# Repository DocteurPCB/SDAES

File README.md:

# SDAES — cartouche SD pour Neo Geo AES

Cartouche ouverte pour Neo Geo **AES** qui charge les jeux depuis une carte
microSD, dans l'esprit de la NeoSD : un menu s'affiche sur la console, on
choisit un fichier `.neo`, la cartouche le charge en mémoire et la console
redémarre dessus. **Tous les composants se soudent au fer** : aucun BGA ni
QFN.

> **État : conception + logiciel vérifiés en simulation, pas encore de
> prototype matériel.** Le code FPGA, le menu, le firmware et les outils sont
> écrits et testés automatiquement (voir plus bas) ; les circuits imprimés
> restent à dessiner. Le brochage AES est relevé sur le wiki neogeodev
> (`hardware/aes_connector.csv`) ; son orientation reste à confirmer sur une
> vraie cartouche (`docs/07-validation-et-feuille-de-route.md`).

## Principe

* **4 FPGA Lattice iCE40 en TQFP-144** (un par bus de la console : programme
  68000, son ADPCM, sprites, couche fixe + Z80) répondent en temps réel et
  remplacent les ROM et les puces de cartouche (NEO-273, NEO-ZMC2,
  NEO-PCM2, banques P et Z80). Chaîne de développement libre (Yosys,
  nextpnr).
* **3 SDRAM + 1 SRAM en TSOP** contiennent le jeu (jusqu'à 24 Mo de P,
  32 Mo de V, 64 Mo de C : tous les jeux commerciaux standards).
* Un **Raspberry Pi Pico 2 (RP2350, ~5 €)** lit la carte SD et charge les
  jeux (~9 Mo/s). Un Raspberry Pi « Linux » ne convient pas pour le bus
  lui-même (trop peu de GPIO, latence) : voir `docs/01-architecture.md`.
* Coût matière estimé : **≈ 70-95 € par cartouche** en petite série,
  montage à la main.

## Organisation du dépôt

| Dossier | Contenu |
|---|---|
| `docs/` | architecture, signaux, timings, liaison, menu/firmware, nomenclature, validation |
| `hdl/` | Verilog des 4 FPGA (`prog/` : P et V, `cha/` : C et SM, `common/`) + bancs de test (`sim/`) |
| `menu/` | menu Neo Geo : programme 68000 (`68k/`) et pilote Z80 (`z80/`) |
| `firmware/rp2350/` | firmware du Pico 2 (SDK Pico + FatFs SDIO) et test sur PC |
| `protocol/` | protocole menu ↔ RP2350, partagé |
| `tools/` | `neotool.py` (.neo, police, BRAM, code de sécurité, bootlegs avec `mame_sets.py`), tests |
| `hardware/` | brochage du connecteur AES (`aes_connector.csv`), gabarits de contraintes FPGA (`.pcf`), futurs projets KiCad |

## Construire et tester

Dépendances (Ubuntu/Debian) : `iverilog`, `gcc-m68k-linux-gnu`, `z80asm`,
`console-setup-linux` (police), Python 3 ; facultatif : `yosys` +
`nextpnr-ice40` (ou `pip install yowasp-yosys yowasp-nextpnr-ice40`),
`pip install machine68k` (émulation du menu).

```
make                               # menu + fichiers d'init BRAM (hdl/build/*.hex)
make SECURITY_FROM=un_jeu.neo      # idem, avec le code de sécurité requis par le BIOS
make test                          # tous les tests (Python + simulations HDL)
make sdaes_test.neo                # ROM de test à copier sur la carte SD
make -C hdl lint pnr YOSYS=yowasp-yosys NEXTPNR=yowasp-nextpnr-ice40   # synthèse + placement-routage des 4 FPGA
python3 tools/neotool.py info jeu.neo
```

Résultats actuels de `make test` :

* 18 tests Python : outils (dont descriptions de protections), firmware sur PC (chargement complet d'un `.neo`
  et comparaison des images mémoire), menu 68000 exécuté dans un émulateur ;
* simulations HDL au niveau carte : `tb_prog` (FPGA P + V) et `tb_cha`
  (FPGA C + SM) en SUCCÈS ; lecture du programme 68000 en 79 ns (126 ns au
  pire cas) pour une limite estimée à ~125-150 ns ;
* placement-routage des 4 FPGA à 101-114 MHz pour 100 MHz visés.

## Documentation

1. [Architecture](docs/01-architecture.md)
2. [Signaux et niveaux 5 V](docs/02-signaux-connecteurs.md)
3. [Mémoires et timings](docs/03-memoire-et-timings.md)
4. [Liaison RP2350 ↔ FPGA](docs/04-liaison-rp2350.md)
5. [Menu et firmware](docs/05-menu-et-firmware.md)
6. [Matériel et nomenclature](docs/06-materiel-nomenclature.md)
7. [Validation et feuille de route](docs/07-validation-et-feuille-de-route.md)
8. [Cartouches protégées](docs/08-cartouches-protegees.md)

## Avertissements

* Aucun BIOS, ROM ou code SNK n'est inclus. Le code de sécurité exigé par le
  BIOS est recopié, à la construction, depuis un jeu que vous possédez.
* Protections : SMA (KOF 99, Garou, Metal Slug 3, KOF 2000), PVC (Metal
  Slug 5, SVC Chaos, KOF 2003), KOF 98, PRO-CT0 (Fatal Fury 2, Super
  Sidekicks), Metal Slug X (P1 corrigée au chargement), Metal Slug 5 Plus
  et les bootlegs de Metal Slug 5, SVC Chaos et KOF 2003 sont pris en
  charge (`neotool mame` fabrique leurs `.neo`)
  ([détails](docs/08-cartouches-protegees.md)) ; les tables SMA s'extraient
  du source de MAME avec `neotool.py sma-from-mame`. Banques de couche fixe
  NEO-CMC : KOF 2000, SVC, KOF 2003, Metal Slug 3/4 ; approchées pour Garou.

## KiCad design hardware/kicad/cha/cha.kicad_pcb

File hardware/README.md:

# Matériel

Contraintes des 4 FPGA iCE40HX4K-TQ144 avec les **vrais numéros de
broches**, produites par `hardware/gen/fpga_pins.py` (ne pas modifier les
`.pcf` à la main) :

```
python3 hardware/gen/fpga_pins.py
make -C hdl pnr YOSYS=yowasp-yosys NEXTPNR=yowasp-nextpnr-ice40
```

| FPGA | Carte | E/S utilisées | Fréquence max (broches réelles) |
|---|---|---|---|
| P | PROG | 94 / 107 | 103,3 MHz |
| V | PROG | 80 / 107 | 102,2 MHz |
| C | CHA | 89 / 107 | 107,6 MHz |
| SM | CHA | 92 / 107 | 108,8 MHz |

## Règles de placement des broches

* Signaux du connecteur (via les tampons de niveaux) sur les bancs 3 et 2
  (côtés gauche et bas du boîtier) ; mémoire, liaison RP2350, MODE et LED
  sur les bancs 0 et 1.
* `CLK25` sur l'entrée globale GBIN3 (broche 93).
* Broche 129 réservée à une sortie : la PLL du haut, utilisée par le
  design, réquisitionne son chemin d'entrée (de même la broche 49 pour la
  PLL du bas).
* Pas de flash : le RP2350 configure les FPGA en SPI esclave par le bus
  de liaison. `LK_SCK` sur la broche 70 (SCK), `LK_IO[0]` sur 68 (SDI),
  `LK_CS_N` sur 71 (SS) ; elles redeviennent ces entrées après la
  configuration. 67 (SDO) ne sert qu'au connecteur de secours.
* Signaux utilisés **comme horloges** dans le HDL — à placer sur des
  entrées globales (GBIN) : `CLK_12M`, `PCK1B` (FPGA C) ; `PCK2B` (SM) ;
  `SDRMPX`, `SDPMPX` (V).
* SDRAM regroupée sur un même côté du boîtier, `SD_CLK` en sortie DDR
  (SB_IO) avec résistance série.
* Bancs d'E/S en 3,3 V ; VPP de l'iCE40 relié au 3,3 V.

## Schémas KiCad (cartes PROG et CHA)

Les schémas sont **générés** à partir d'une description Python des deux
cartes (`hardware/gen/boards.py`), puis vérifiés par KiCad :

```
sudo apt-get install kicad kicad-symbols kicad-footprints     # KiCad 7
python3 hardware/gen/boards.py --check --pdf
```

* `hardware/kicad/prog/`, `hardware/kicad/cha/` : projets KiCad (une
  feuille par bloc : connecteur et alimentations, tampons de niveaux,
  FPGA, mémoires, RP2350 et carte SD).
* `hardware/kicad/sdaes_prog.pdf`, `sdaes_cha.pdf` : schémas en PDF.
* `hardware/kicad/sdaes.kicad_sym`, `sdaes.pretty` : symboles et empreintes
  propres au projet (connecteur de bord AES, Pico 2, 16244, SRAM).
* `--check` réexporte la netlist avec `kicad-cli` et la compare à la
  description : elle doit être **identique** (aucun réseau oublié ni
  ajouté). Aucun réseau ne doit toucher une seule broche.

Chaque broche porte une étiquette globale au nom de son signal (pas de
fils) : `AES_xxx` côté console (5 V), `xxx` côté FPGA, `P_`, `V_`, `C_`,
`SM_` pour les signaux locaux d'un FPGA. Les broches des FPGA viennent des
`.pcf` ci-dessus. Brochages hors bibliothèque KiCad relevés dans les fiches
TI (SN74LVC16244A, SN74AHCT16244 : identiques), ISSI (IS61WV10248EDBLL) et
Raspberry Pi (Pico 2).

| Carte | Composants | Réseaux |
|---|---|---|
| PROG | 124 | 274 |
| CHA | 138 | 293 |

Par FPGA : connecteur de secours 2 x 3 (configuration directe par
`iceprog -S`, RP2350 au repos), oscillateur 25 MHz, filtre RC des deux PLL
(100 Ω, 10 µF, 100 nF), découplage 100 nF par broche d'alimentation, LED.
Alimentations par carte : AMS1117-3.3 (5 V → 3,3 V) et AP2112K-1.2
(3,3 V → 1,2 V).

### Contours et connecteur de bord

`python3 hardware/gen/outline.py` (module Python de KiCad) écrit
`hardware/kicad/{prog,cha}/{prog,cha}.kicad_pcb` : contour, deux trous de
10 mm pour les plots de la coque et connecteur J1 placé. Cotes reprises des
cartes AES de jwestfall69 (`neogeo-diag-aes-prog`, `neogeo-diag-aes-cha`,
fabriquées et testées, domaine public ; ce sont des cartes de test du Z80,
reprises pour leur mécanique seulement), identiques à 0,01 mm près, et
recoupées sur la photo de la carte SNK NEO-AEG PROG-EP du wiki :

| | PROG | CHA |
|---|---|---|
| Corps | 174,0 x 115 mm | 173,0 x 115 mm |
| Languette (centrée) | 129,2 x 19 mm | 129,2 x 19 mm |
| Encoches 12 x 2,5 mm (bord supérieur) | à 36 mm de chaque bord | à 5,45 mm de chaque bord |
| Trous Ø 10 mm | ±45 mm de l'axe, 11,75 mm au-dessus de l'épaulement | idem |

Contacts : 1,5 x 10 mm au pas de 2,54 mm, centre à 7,1 mm du bord ; A1..A50
(repères T) sur la face composants, B1..B50 sur l'autre ; vu côté
composants, languette en bas, A1 et B1 à droite. Fabrication : 1,6 mm,
finition ENIG, contacts dorés chanfreinés à 45° : déclaré dans l'empilement
de la carte (connecteur de bord biseauté, repris dans le fichier `.gbrjob`)
et rappelé par une note sur la couche Cmts.User ; option « Gold fingers » +
« Beveled » à cocher à la commande. La carte CHA se loge
derrière la carte PROG : hauteur des composants limitée (jwestfall69 :
un support DIP ordinaire + EPROM est trop haut, un support bas passe).

### Circuits imprimés (4 couches)

```
python3 hardware/gen/pcb.py --pins     # placement + affectation des broches FPGA
python3 hardware/gen/fpga_pins.py      # .pcf (pins_opt.json prioritaire)
python3 hardware/gen/boards.py --check # schémas à jour
python3 hardware/gen/pcb.py            # placement final (répéter jusqu'à stabilité)
python3 hardware/gen/route.py prog     # Freerouting puis DRC (idem cha)
```

* `pcb.py` : empreintes et réseaux depuis `boards.py`, contour depuis
  `outline.py`. Ancres (circuits intégrés, connecteurs) à des positions
  fixées : contacts en bas, tampons de niveaux en rangée au-dessus (canaux
  dans l'ordre des contacts), FPGA au milieu, mémoires en haut ; carte PROG
  (côté avant de la cartouche) : Pico 2 au milieu, microSD et bouton sur le
  bord supérieur ; sous le Pico, ni piste ni via sur la face composants.
  Câble PROG-CHA au même endroit sur les deux cartes (x = 172 mm). Passifs placés au plus près de la broche de
  leur circuit. Empilement : F.Cu signaux, In1 plan de masse continu,
  In2 plan +3V3, B.Cu signaux ; +5V et +1V2 en pistes larges. Le 4
  couches est retenu pour la SDRAM à 100 MHz (fronts ~1 ns : chemin de
  retour sous chaque piste) et le découplage des FPGA ; surcoût de quelques
  euros par cartouche.
* `--pins` : chaque signal d'un FPGA est affecté à la broche tournée vers
  sa cible, en conservant l'ordre circulaire (pas de croisement à la
  sortie du boîtier) ; horloges sur leurs entrées GBIN, broche 129 en
  sortie seulement. Résultat dans `hardware/gen/pins_opt.json`, repris par
  `fpga_pins.py` ; le placement-routage FPGA (`make -C hdl pnr`) doit être
  relancé ensuite.
* `route.py` : export Specctra (couches internes déclarées « power »),
  Freerouting (2.4.1, Java 25), relecture de la session, remplissage des
  zones, DRC `kicad-cli`.

**À vérifier avant le routage** : boucles audio L/R reliées par
des résistances de 0 Ω (révision NEO-AES de la console), valeurs du filtre
PLL (note Lattice sur l'iCE40), courant réel des régulateurs.

## À faire

1. ~~Brochage et cotes des cartes AES PROG/CHA~~ (fait, voir plus haut).
2. ~~Schémas~~, ~~contours~~ (faits).
3. Routage 4 couches (en cours, `route.py`), contacts dorés chanfreinés.
4. Après un premier routage : remplacer la nappe PROG-CHA (J2 / J5, 2 x 7)
   par un connecteur carte à carte aligné sur les deux cartes, hauteur
   adaptée aux entretoises.
5. `make -C hdl bits` (bitstreams avec les broches réelles).

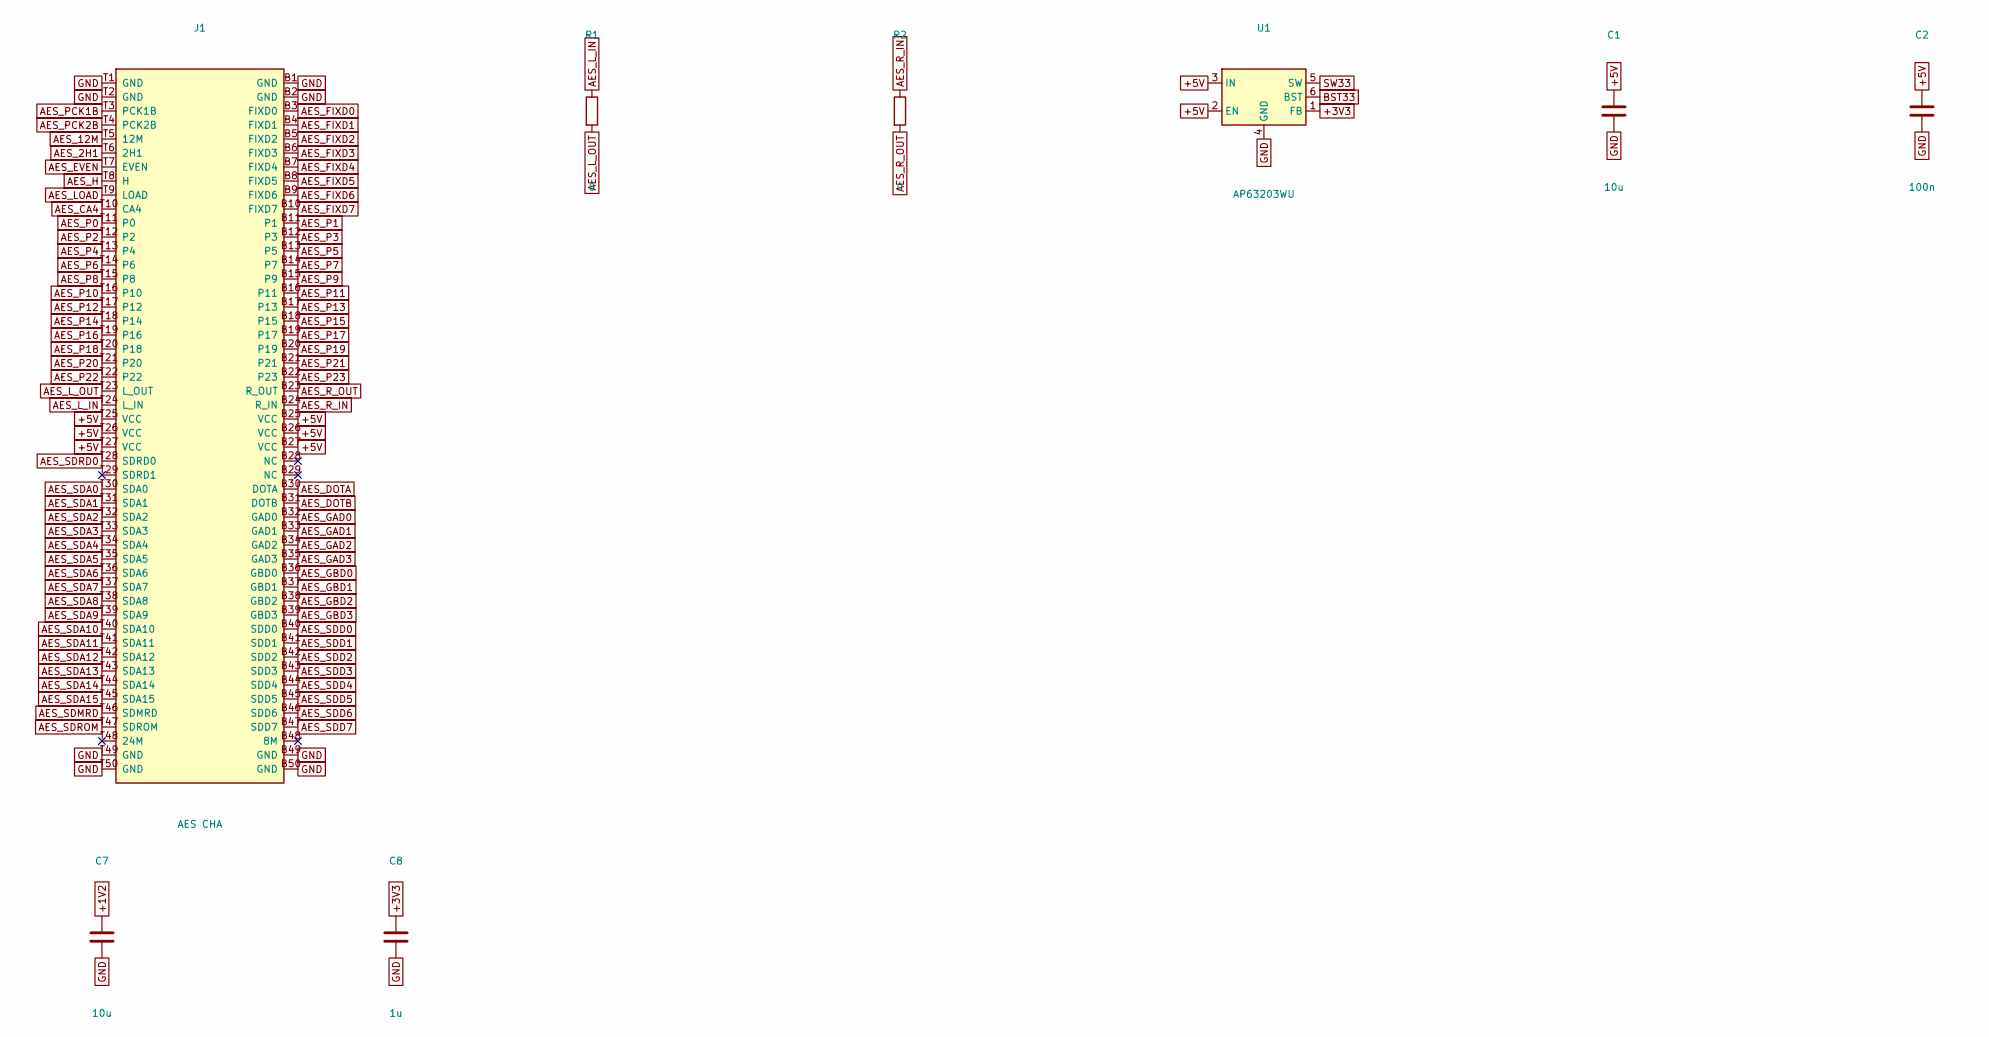
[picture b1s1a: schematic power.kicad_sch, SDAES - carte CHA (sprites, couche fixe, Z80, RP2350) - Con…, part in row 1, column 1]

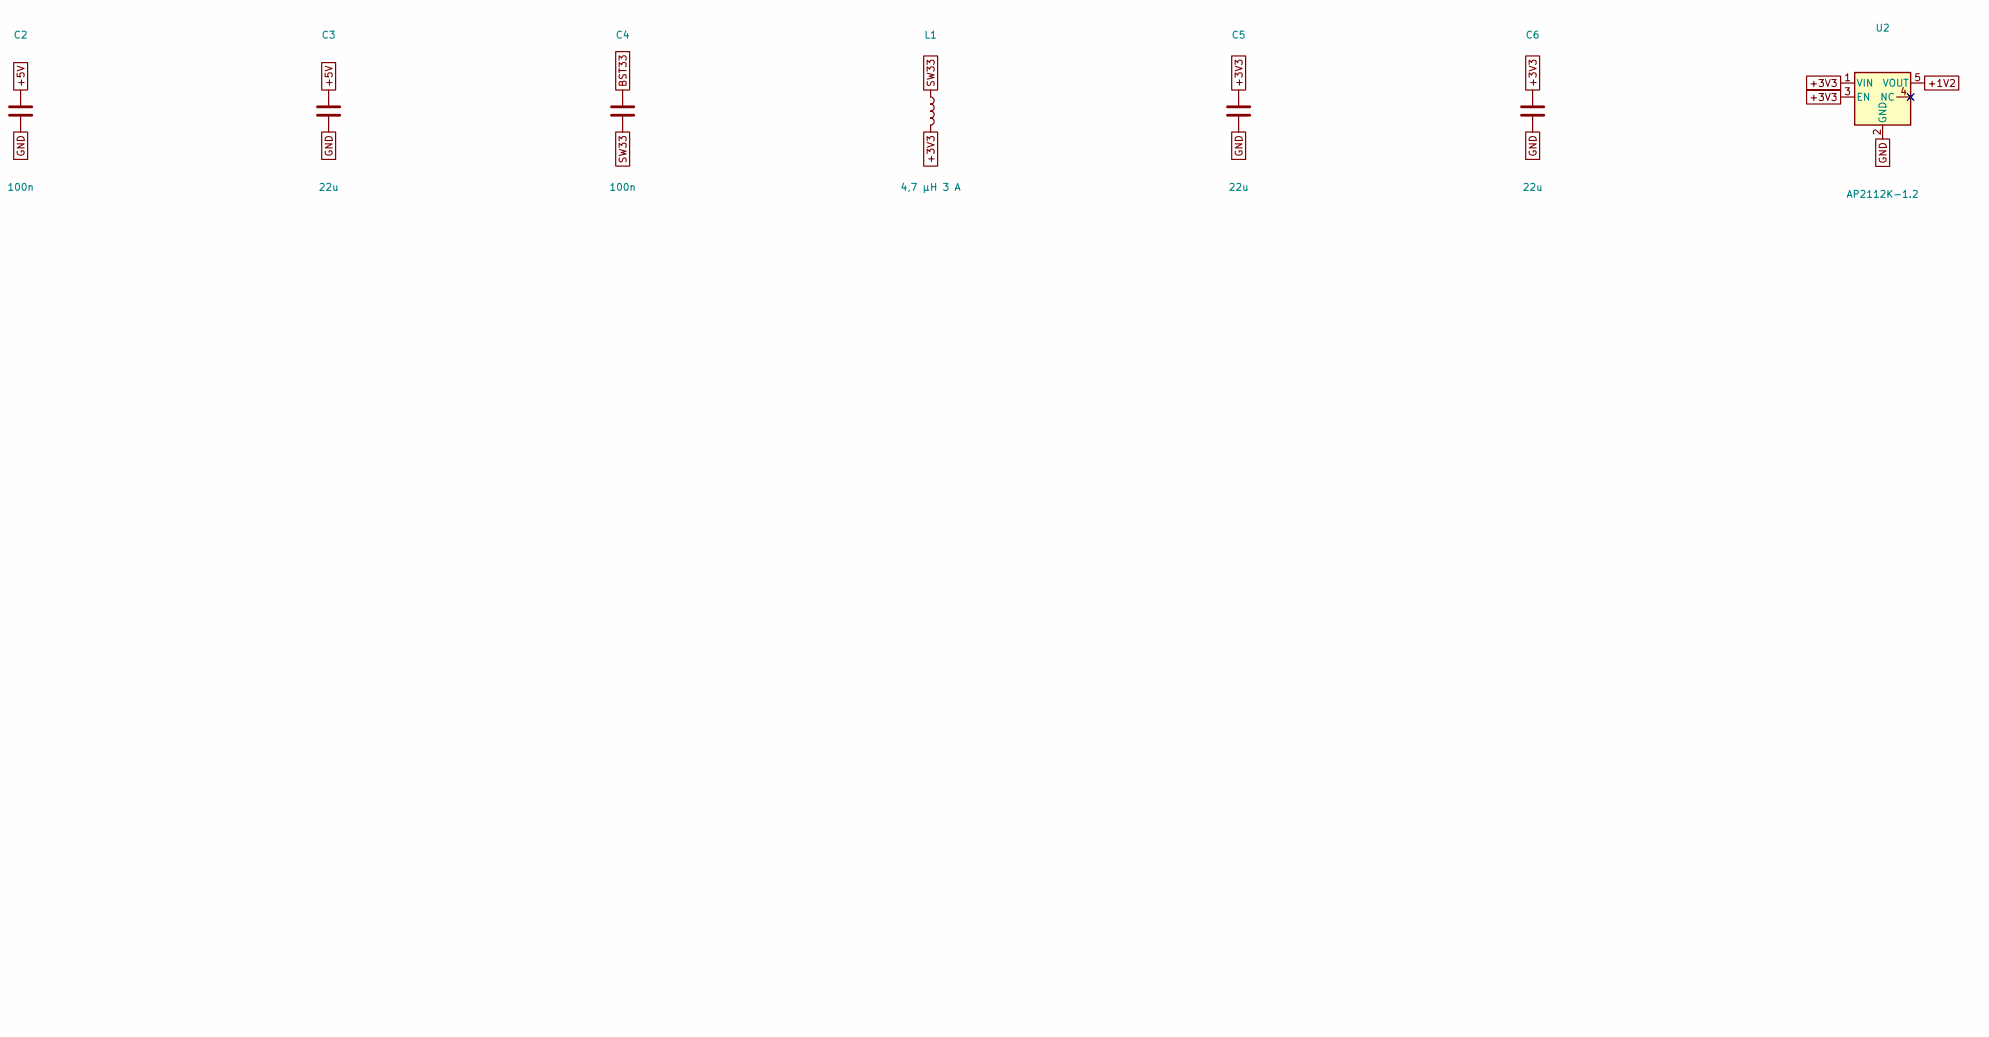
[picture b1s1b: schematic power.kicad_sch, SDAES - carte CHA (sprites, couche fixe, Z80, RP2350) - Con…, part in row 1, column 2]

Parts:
C1, C7: 10u; C_0805_2012Metric
C2, C4: 100n; C_0603_1608Metric
C3, C5, C6: 22u; C_1206_3216Metric
C8: 1u; C_0603_1608Metric
J1: AES CHA; AES_Edge_2x50_P2.54mm
L1: 4,7 µH 3 A; L_Bourns_SRP5030T
R1, R2: 0; R_0603_1608Metric
U1: AP63203WU; TSOT-23-6
U2: AP2112K-1.2; SOT-23-5

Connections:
+1V2: C7.1, U2.5 (VOUT); also elsewhere on the board
+3V3: C5.1, C6.1, C8.1, L1.2, U1.1 (FB), U2.1 (VIN), U2.3 (EN); also elsewhere on the board
+5V: C1.1, C2.1, C3.1, J1.B25 (VCC), J1.B26 (VCC), J1.B27 (VCC), J1.T25 (VCC), J1.T26 (VCC), J1.T27 (VCC), U1.2 (EN), U1.3 (IN); also elsewhere on the board
AES_2H1: J1.T6 (2H1); also elsewhere on the board
AES_12M: J1.T5 (12M); also elsewhere on the board
AES_CA4: J1.T10 (CA4); also elsewhere on the board
AES_DOTA: J1.B30 (DOTA); also elsewhere on the board
AES_DOTB: J1.B31 (DOTB); also elsewhere on the board
AES_EVEN: J1.T7 (EVEN); also elsewhere on the board
AES_FIXD0: J1.B3 (FIXD0); also elsewhere on the board
AES_FIXD1: J1.B4 (FIXD1); also elsewhere on the board
AES_FIXD2: J1.B5 (FIXD2); also elsewhere on the board
AES_FIXD3: J1.B6 (FIXD3); also elsewhere on the board
AES_FIXD4: J1.B7 (FIXD4); also elsewhere on the board
AES_FIXD5: J1.B8 (FIXD5); also elsewhere on the board
AES_FIXD6: J1.B9 (FIXD6); also elsewhere on the board
AES_FIXD7: J1.B10 (FIXD7); also elsewhere on the board
AES_GAD0: J1.B32 (GAD0); also elsewhere on the board
AES_GAD1: J1.B33 (GAD1); also elsewhere on the board
AES_GAD2: J1.B34 (GAD2); also elsewhere on the board
AES_GAD3: J1.B35 (GAD3); also elsewhere on the board
AES_GBD0: J1.B36 (GBD0); also elsewhere on the board
AES_GBD1: J1.B37 (GBD1); also elsewhere on the board
AES_GBD2: J1.B38 (GBD2); also elsewhere on the board
AES_GBD3: J1.B39 (GBD3); also elsewhere on the board
AES_H: J1.T8 (H); also elsewhere on the board
AES_LOAD: J1.T9 (LOAD); also elsewhere on the board
AES_L_IN: J1.T24 (L_IN), R1.1
AES_L_OUT: J1.T23 (L_OUT), R1.2
AES_P0: J1.T11 (P0); also elsewhere on the board
AES_P1: J1.B11 (P1); also elsewhere on the board
AES_P2: J1.T12 (P2); also elsewhere on the board
AES_P3: J1.B12 (P3); also elsewhere on the board
AES_P4: J1.T13 (P4); also elsewhere on the board
AES_P5: J1.B13 (P5); also elsewhere on the board
AES_P6: J1.T14 (P6); also elsewhere on the board
AES_P7: J1.B14 (P7); also elsewhere on the board
AES_P8: J1.T15 (P8); also elsewhere on the board
AES_P9: J1.B15 (P9); also elsewhere on the board
AES_P10: J1.T16 (P10); also elsewhere on the board
AES_P11: J1.B16 (P11); also elsewhere on the board
AES_P12: J1.T17 (P12); also elsewhere on the board
AES_P13: J1.B17 (P13); also elsewhere on the board
AES_P14: J1.T18 (P14); also elsewhere on the board
AES_P15: J1.B18 (P15); also elsewhere on the board
AES_P16: J1.T19 (P16); also elsewhere on the board
AES_P17: J1.B19 (P17); also elsewhere on the board
AES_P18: J1.T20 (P18); also elsewhere on the board
AES_P19: J1.B20 (P19); also elsewhere on the board
AES_P20: J1.T21 (P20); also elsewhere on the board
AES_P21: J1.B21 (P21); also elsewhere on the board
AES_P22: J1.T22 (P22); also elsewhere on the board
AES_P23: J1.B22 (P23); also elsewhere on the board
AES_PCK1B: J1.T3 (PCK1B); also elsewhere on the board
AES_PCK2B: J1.T4 (PCK2B); also elsewhere on the board
AES_R_IN: J1.B24 (R_IN), R2.1
AES_R_OUT: J1.B23 (R_OUT), R2.2
AES_SDA0: J1.T30 (SDA0); also elsewhere on the board
AES_SDA1: J1.T31 (SDA1); also elsewhere on the board
AES_SDA2: J1.T32 (SDA2); also elsewhere on the board
AES_SDA3: J1.T33 (SDA3); also elsewhere on the board
AES_SDA4: J1.T34 (SDA4); also elsewhere on the board
AES_SDA5: J1.T35 (SDA5); also elsewhere on the board
AES_SDA6: J1.T36 (SDA6); also elsewhere on the board
AES_SDA7: J1.T37 (SDA7); also elsewhere on the board
AES_SDA8: J1.T38 (SDA8); also elsewhere on the board
AES_SDA9: J1.T39 (SDA9); also elsewhere on the board
AES_SDA10: J1.T40 (SDA10); also elsewhere on the board
AES_SDA11: J1.T41 (SDA11); also elsewhere on the board
AES_SDA12: J1.T42 (SDA12); also elsewhere on the board
AES_SDA13: J1.T43 (SDA13); also elsewhere on the board
AES_SDA14: J1.T44 (SDA14); also elsewhere on the board
AES_SDA15: J1.T45 (SDA15); also elsewhere on the board
AES_SDD0: J1.B40 (SDD0); also elsewhere on the board
AES_SDD1: J1.B41 (SDD1); also elsewhere on the board
AES_SDD2: J1.B42 (SDD2); also elsewhere on the board
AES_SDD3: J1.B43 (SDD3); also elsewhere on the board
AES_SDD4: J1.B44 (SDD4); also elsewhere on the board
AES_SDD5: J1.B45 (SDD5); also elsewhere on the board
AES_SDD6: J1.B46 (SDD6); also elsewhere on the board
AES_SDD7: J1.B47 (SDD7); also elsewhere on the board
AES_SDMRD: J1.T46 (SDMRD); also elsewhere on the board
AES_SDRD0: J1.T28 (SDRD0); also elsewhere on the board
AES_SDROM: J1.T47 (SDROM); also elsewhere on the board
BST33: C4.1, U1.6 (BST)
GND: C1.2, C2.2, C3.2, C5.2, C6.2, C7.2, C8.2, J1.B1 (GND), J1.B2 (GND), J1.B49 (GND), J1.B50 (GND), J1.T1 (GND), J1.T2 (GND), J1.T49 (GND), J1.T50 (GND), U1.4 (GND), U2.2 (GND); also elsewhere on the board
SW33: C4.2, L1.1, U1.5 (SW)

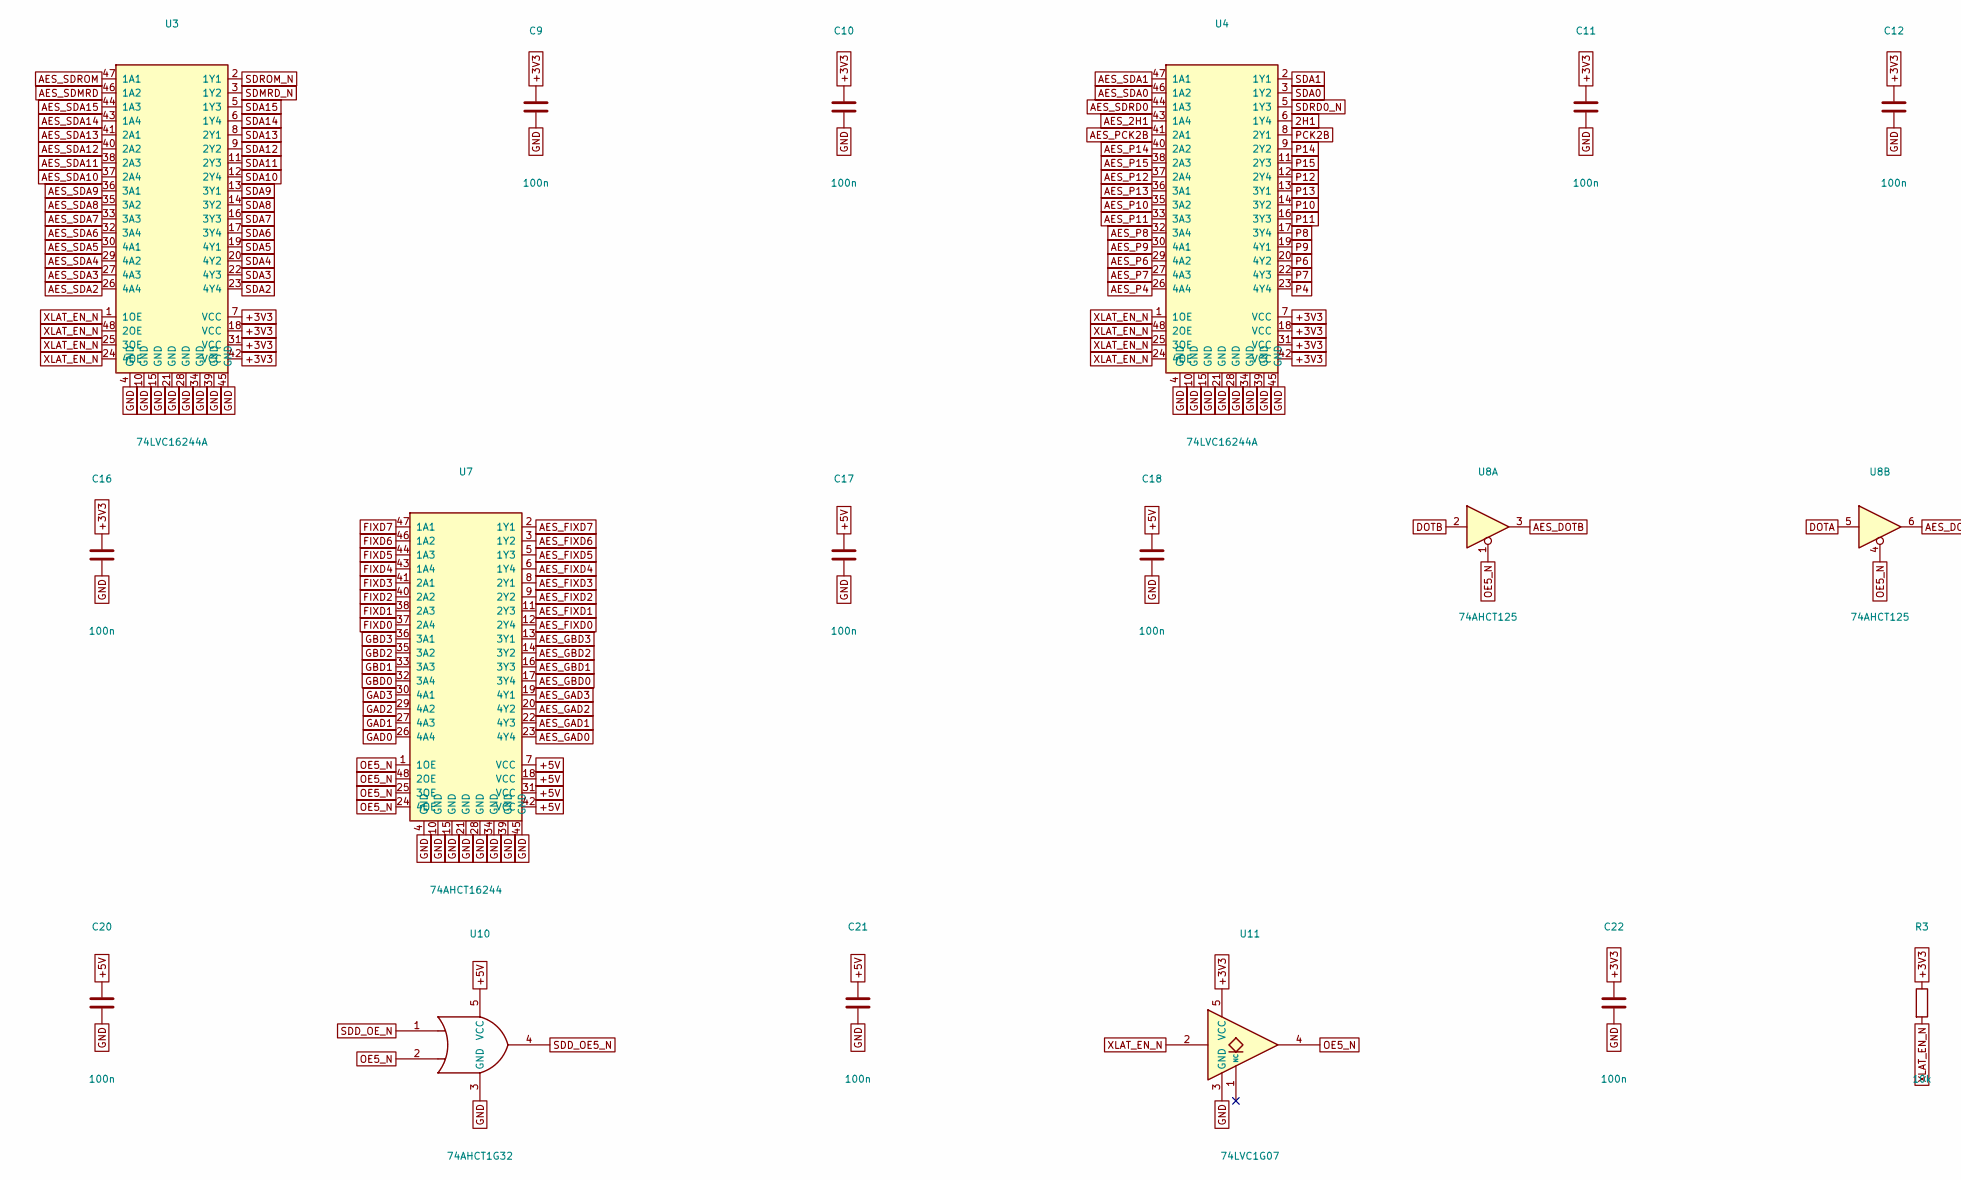
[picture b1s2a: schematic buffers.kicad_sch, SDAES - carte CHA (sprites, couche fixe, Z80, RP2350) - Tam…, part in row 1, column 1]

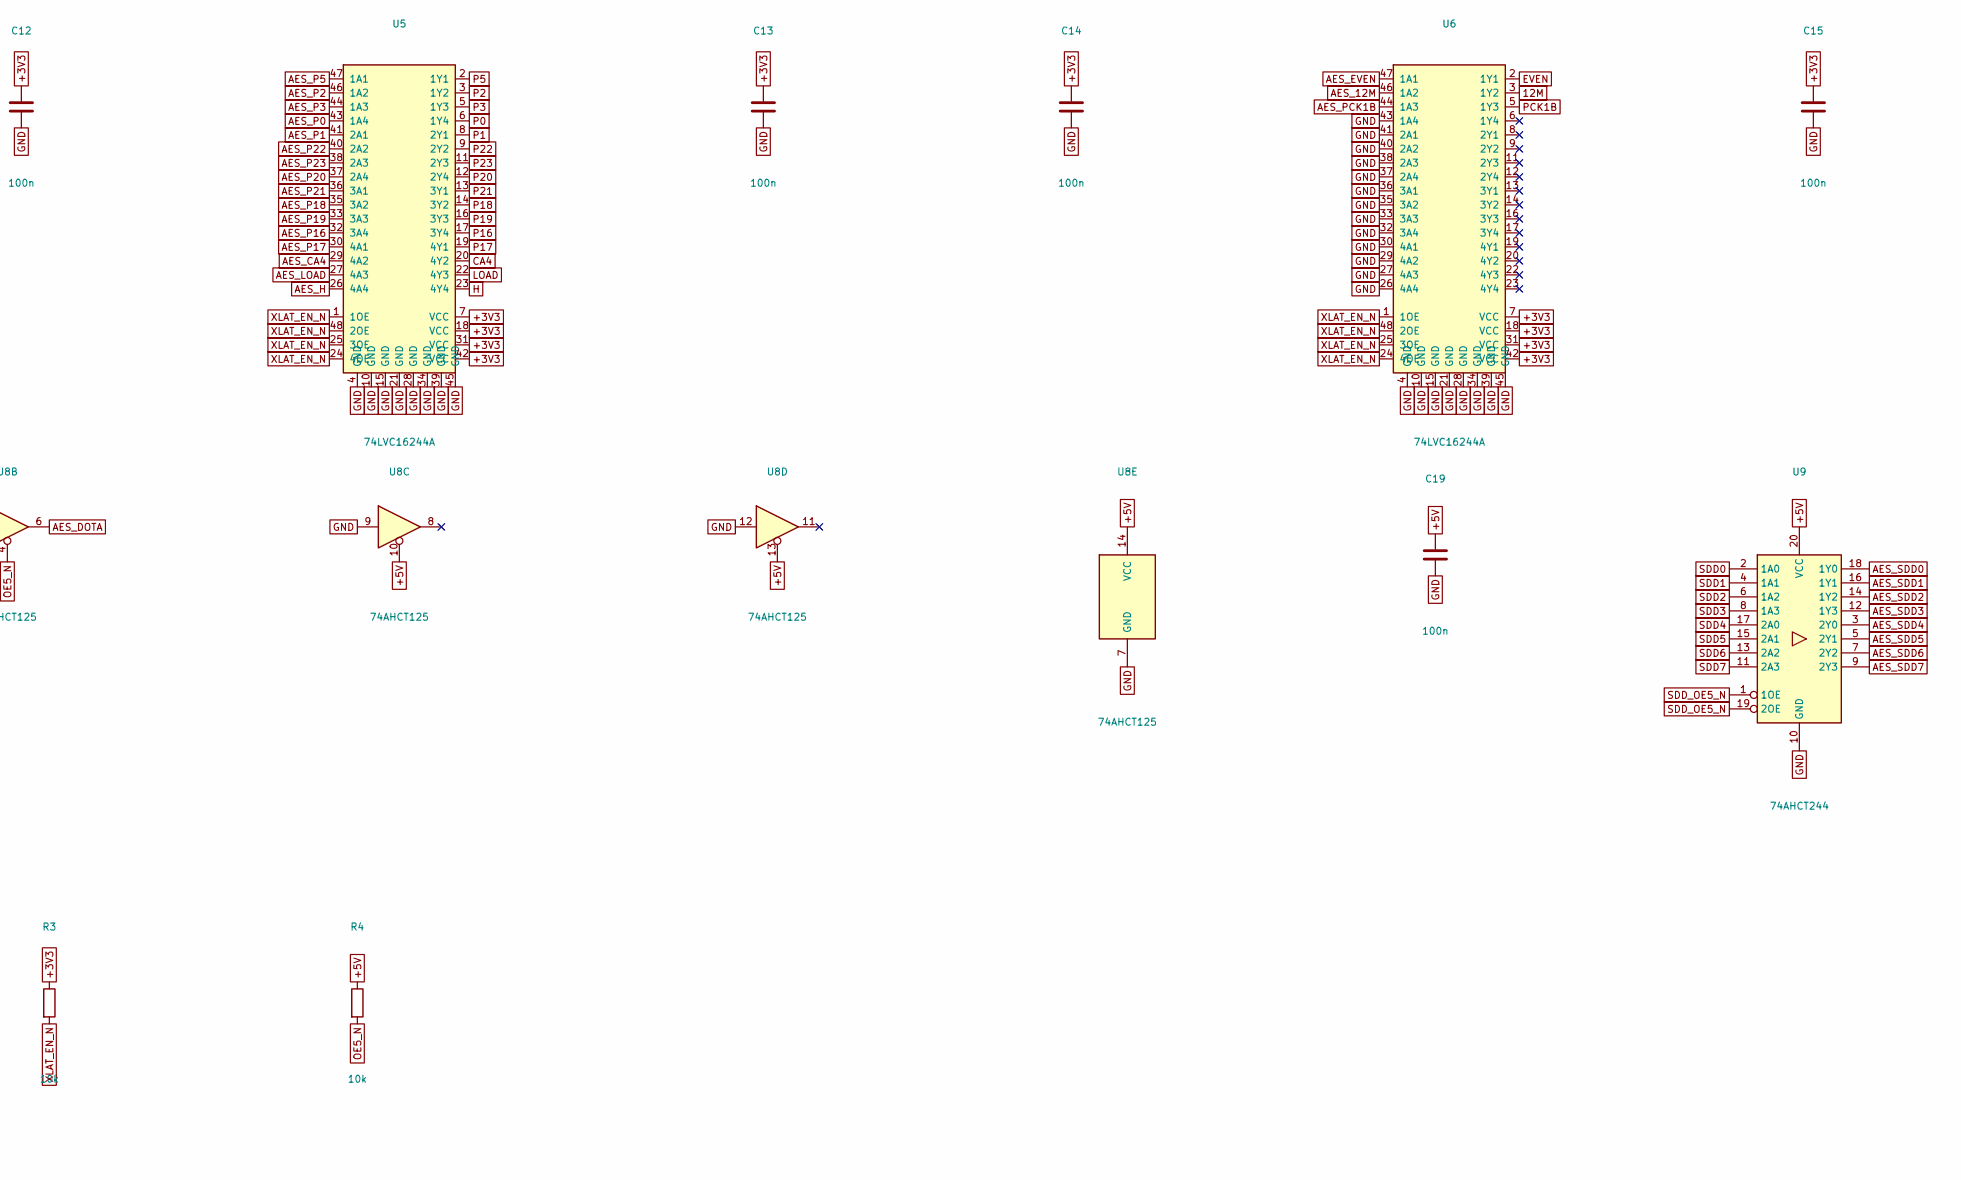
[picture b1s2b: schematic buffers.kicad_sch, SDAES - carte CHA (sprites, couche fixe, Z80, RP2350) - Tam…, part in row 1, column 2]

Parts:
C9, C10, C11, C12, C13, C14, C15, C16, C17, C18, C19, C20, C21, C22: 100n; C_0603_1608Metric
R3, R4: 10k; R_0603_1608Metric
U3, U4, U5, U6: 74LVC16244A; TSSOP-48_6.1x12.5mm_P0.5mm
U7: 74AHCT16244; TSSOP-48_6.1x12.5mm_P0.5mm
U8: 74AHCT125; TSSOP-14_4.4x5mm_P0.65mm
U9: 74AHCT244; TSSOP-20_4.4x6.5mm_P0.65mm
U10: 74AHCT1G32; SOT-23-5
U11: 74LVC1G07; SOT-23-5

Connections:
2H1: U4.6 (1Y4); also elsewhere on the board
12M: U6.3 (1Y2); also elsewhere on the board
+3V3: C9.1, C10.1, C11.1, C12.1, C13.1, C14.1, C15.1, C16.1, C22.1, R3.1, U3.7 (VCC), U3.18 (VCC), U3.31 (VCC), U3.42 (VCC), U4.7 (VCC), U4.18 (VCC), U4.31 (VCC), U4.42 (VCC), U5.7 (VCC), U5.18 (VCC), U5.31 (VCC), U5.42 (VCC), U6.7 (VCC), U6.18 (VCC), U6.31 (VCC), U6.42 (VCC), U11.5 (VCC); also elsewhere on the board
+5V: C17.1, C18.1, C19.1, C20.1, C21.1, R4.1, U7.7 (VCC), U7.18 (VCC), U7.31 (VCC), U7.42 (VCC), U8.10, U8.13, U8.14 (VCC), U9.20 (VCC), U10.5 (VCC); also elsewhere on the board
AES_2H1: U4.43 (1A4); also elsewhere on the board
AES_12M: U6.46 (1A2); also elsewhere on the board
AES_CA4: U5.29 (4A2); also elsewhere on the board
AES_DOTA: U8.6; also elsewhere on the board
AES_DOTB: U8.3; also elsewhere on the board
AES_EVEN: U6.47 (1A1); also elsewhere on the board
AES_FIXD0: U7.12 (2Y4); also elsewhere on the board
AES_FIXD1: U7.11 (2Y3); also elsewhere on the board
AES_FIXD2: U7.9 (2Y2); also elsewhere on the board
AES_FIXD3: U7.8 (2Y1); also elsewhere on the board
AES_FIXD4: U7.6 (1Y4); also elsewhere on the board
AES_FIXD5: U7.5 (1Y3); also elsewhere on the board
AES_FIXD6: U7.3 (1Y2); also elsewhere on the board
AES_FIXD7: U7.2 (1Y1); also elsewhere on the board
AES_GAD0: U7.23 (4Y4); also elsewhere on the board
AES_GAD1: U7.22 (4Y3); also elsewhere on the board
AES_GAD2: U7.20 (4Y2); also elsewhere on the board
AES_GAD3: U7.19 (4Y1); also elsewhere on the board
AES_GBD0: U7.17 (3Y4); also elsewhere on the board
AES_GBD1: U7.16 (3Y3); also elsewhere on the board
AES_GBD2: U7.14 (3Y2); also elsewhere on the board
AES_GBD3: U7.13 (3Y1); also elsewhere on the board
AES_H: U5.26 (4A4); also elsewhere on the board
AES_LOAD: U5.27 (4A3); also elsewhere on the board
AES_P0: U5.43 (1A4); also elsewhere on the board
AES_P1: U5.41 (2A1); also elsewhere on the board
AES_P2: U5.46 (1A2); also elsewhere on the board
AES_P3: U5.44 (1A3); also elsewhere on the board
AES_P4: U4.26 (4A4); also elsewhere on the board
AES_P5: U5.47 (1A1); also elsewhere on the board
AES_P6: U4.29 (4A2); also elsewhere on the board
AES_P7: U4.27 (4A3); also elsewhere on the board
AES_P8: U4.32 (3A4); also elsewhere on the board
AES_P9: U4.30 (4A1); also elsewhere on the board
AES_P10: U4.35 (3A2); also elsewhere on the board
AES_P11: U4.33 (3A3); also elsewhere on the board
AES_P12: U4.37 (2A4); also elsewhere on the board
AES_P13: U4.36 (3A1); also elsewhere on the board
AES_P14: U4.40 (2A2); also elsewhere on the board
AES_P15: U4.38 (2A3); also elsewhere on the board
AES_P16: U5.32 (3A4); also elsewhere on the board
AES_P17: U5.30 (4A1); also elsewhere on the board
AES_P18: U5.35 (3A2); also elsewhere on the board
AES_P19: U5.33 (3A3); also elsewhere on the board
AES_P20: U5.37 (2A4); also elsewhere on the board
AES_P21: U5.36 (3A1); also elsewhere on the board
AES_P22: U5.40 (2A2); also elsewhere on the board
AES_P23: U5.38 (2A3); also elsewhere on the board
AES_PCK1B: U6.44 (1A3); also elsewhere on the board
AES_PCK2B: U4.41 (2A1); also elsewhere on the board
AES_SDA0: U4.46 (1A2); also elsewhere on the board
AES_SDA1: U4.47 (1A1); also elsewhere on the board
AES_SDA2: U3.26 (4A4); also elsewhere on the board
AES_SDA3: U3.27 (4A3); also elsewhere on the board
AES_SDA4: U3.29 (4A2); also elsewhere on the board
AES_SDA5: U3.30 (4A1); also elsewhere on the board
AES_SDA6: U3.32 (3A4); also elsewhere on the board
AES_SDA7: U3.33 (3A3); also elsewhere on the board
AES_SDA8: U3.35 (3A2); also elsewhere on the board
AES_SDA9: U3.36 (3A1); also elsewhere on the board
AES_SDA10: U3.37 (2A4); also elsewhere on the board
AES_SDA11: U3.38 (2A3); also elsewhere on the board
AES_SDA12: U3.40 (2A2); also elsewhere on the board
AES_SDA13: U3.41 (2A1); also elsewhere on the board
AES_SDA14: U3.43 (1A4); also elsewhere on the board
AES_SDA15: U3.44 (1A3); also elsewhere on the board
AES_SDD0: U9.18 (1Y0); also elsewhere on the board
AES_SDD1: U9.16 (1Y1); also elsewhere on the board
AES_SDD2: U9.14 (1Y2); also elsewhere on the board
AES_SDD3: U9.12 (1Y3); also elsewhere on the board
AES_SDD4: U9.3 (2Y0); also elsewhere on the board
AES_SDD5: U9.5 (2Y1); also elsewhere on the board
AES_SDD6: U9.7 (2Y2); also elsewhere on the board
AES_SDD7: U9.9 (2Y3); also elsewhere on the board
AES_SDMRD: U3.46 (1A2); also elsewhere on the board
AES_SDRD0: U4.44 (1A3); also elsewhere on the board
AES_SDROM: U3.47 (1A1); also elsewhere on the board
CA4: U5.20 (4Y2); also elsewhere on the board
DOTA: U8.5; also elsewhere on the board
DOTB: U8.2; also elsewhere on the board
EVEN: U6.2 (1Y1); also elsewhere on the board
FIXD0: U7.37 (2A4); also elsewhere on the board
FIXD1: U7.38 (2A3); also elsewhere on the board
FIXD2: U7.40 (2A2); also elsewhere on the board
FIXD3: U7.41 (2A1); also elsewhere on the board
FIXD4: U7.43 (1A4); also elsewhere on the board
FIXD5: U7.44 (1A3); also elsewhere on the board
FIXD6: U7.46 (1A2); also elsewhere on the board
FIXD7: U7.47 (1A1); also elsewhere on the board
GAD0: U7.26 (4A4); also elsewhere on the board
GAD1: U7.27 (4A3); also elsewhere on the board
GAD2: U7.29 (4A2); also elsewhere on the board
GAD3: U7.30 (4A1); also elsewhere on the board
GBD0: U7.32 (3A4); also elsewhere on the board
GBD1: U7.33 (3A3); also elsewhere on the board
GBD2: U7.35 (3A2); also elsewhere on the board
GBD3: U7.36 (3A1); also elsewhere on the board
GND: C9.2, C10.2, C11.2, C12.2, C13.2, C14.2, C15.2, C16.2, C17.2, C18.2, C19.2, C20.2, C21.2, C22.2, U3.4 (GND), U3.10 (GND), U3.15 (GND), U3.21 (GND), U3.28 (GND), U3.34 (GND), U3.39 (GND), U3.45 (GND), U4.4 (GND), U4.10 (GND), U4.15 (GND), U4.21 (GND), U4.28 (GND), U4.34 (GND), U4.39 (GND), U4.45 (GND), U5.4 (GND), U5.10 (GND), U5.15 (GND), U5.21 (GND), U5.28 (GND), U5.34 (GND), U5.39 (GND), U5.45 (GND), U6.4 (GND), U6.10 (GND), U6.15 (GND), U6.21 (GND), U6.26 (4A4), U6.27 (4A3), U6.28 (GND), U6.29 (4A2), U6.30 (4A1), U6.32 (3A4), U6.33 (3A3), U6.34 (GND), U6.35 (3A2), U6.36 (3A1), U6.37 (2A4), U6.38 (2A3), U6.39 (GND), U6.40 (2A2), U6.41 (2A1), U6.43 (1A4), U6.45 (GND), U7.4 (GND), U7.10 (GND), U7.15 (GND), U7.21 (GND), U7.28 (GND), U7.34 (GND), U7.39 (GND), U7.45 (GND), U8.7 (GND), U8.9, U8.12, U9.10 (GND), U10.3 (GND), U11.3 (GND); also elsewhere on the board
H: U5.23 (4Y4); also elsewhere on the board
LOAD: U5.22 (4Y3); also elsewhere on the board
OE5_N: R4.2, U7.1 (1OE), U7.24 (4OE), U7.25 (3OE), U7.48 (2OE), U8.1, U8.4, U10.2, U11.4
P0: U5.6 (1Y4); also elsewhere on the board
P1: U5.8 (2Y1); also elsewhere on the board
P2: U5.3 (1Y2); also elsewhere on the board
P3: U5.5 (1Y3); also elsewhere on the board
P4: U4.23 (4Y4); also elsewhere on the board
P5: U5.2 (1Y1); also elsewhere on the board
P6: U4.20 (4Y2); also elsewhere on the board
P7: U4.22 (4Y3); also elsewhere on the board
P8: U4.17 (3Y4); also elsewhere on the board
P9: U4.19 (4Y1); also elsewhere on the board
P10: U4.14 (3Y2); also elsewhere on the board
P11: U4.16 (3Y3); also elsewhere on the board
P12: U4.12 (2Y4); also elsewhere on the board
P13: U4.13 (3Y1); also elsewhere on the board
P14: U4.9 (2Y2); also elsewhere on the board
P15: U4.11 (2Y3); also elsewhere on the board
P16: U5.17 (3Y4); also elsewhere on the board
P17: U5.19 (4Y1); also elsewhere on the board
P18: U5.14 (3Y2); also elsewhere on the board
P19: U5.16 (3Y3); also elsewhere on the board
P20: U5.12 (2Y4); also elsewhere on the board
P21: U5.13 (3Y1); also elsewhere on the board
P22: U5.9 (2Y2); also elsewhere on the board
P23: U5.11 (2Y3); also elsewhere on the board
PCK1B: U6.5 (1Y3); also elsewhere on the board
PCK2B: U4.8 (2Y1); also elsewhere on the board
SDA0: U4.3 (1Y2); also elsewhere on the board
SDA1: U4.2 (1Y1); also elsewhere on the board
SDA2: U3.23 (4Y4); also elsewhere on the board
SDA3: U3.22 (4Y3); also elsewhere on the board
SDA4: U3.20 (4Y2); also elsewhere on the board
SDA5: U3.19 (4Y1); also elsewhere on the board
SDA6: U3.17 (3Y4); also elsewhere on the board
SDA7: U3.16 (3Y3); also elsewhere on the board
SDA8: U3.14 (3Y2); also elsewhere on the board
SDA9: U3.13 (3Y1); also elsewhere on the board
SDA10: U3.12 (2Y4); also elsewhere on the board
SDA11: U3.11 (2Y3); also elsewhere on the board
SDA12: U3.9 (2Y2); also elsewhere on the board
SDA13: U3.8 (2Y1); also elsewhere on the board
SDA14: U3.6 (1Y4); also elsewhere on the board
SDA15: U3.5 (1Y3); also elsewhere on the board
SDD0: U9.2 (1A0); also elsewhere on the board
SDD1: U9.4 (1A1); also elsewhere on the board
SDD2: U9.6 (1A2); also elsewhere on the board
SDD3: U9.8 (1A3); also elsewhere on the board
SDD4: U9.17 (2A0); also elsewhere on the board
SDD5: U9.15 (2A1); also elsewhere on the board
SDD6: U9.13 (2A2); also elsewhere on the board
SDD7: U9.11 (2A3); also elsewhere on the board
SDD_OE5_N: U9.1 (1OE), U9.19 (2OE), U10.4
SDD_OE_N: U10.1; also elsewhere on the board
SDMRD_N: U3.3 (1Y2); also elsewhere on the board
SDRD0_N: U4.5 (1Y3); also elsewhere on the board
SDROM_N: U3.2 (1Y1); also elsewhere on the board
XLAT_EN_N: R3.2, U3.1 (1OE), U3.24 (4OE), U3.25 (3OE), U3.48 (2OE), U4.1 (1OE), U4.24 (4OE), U4.25 (3OE), U4.48 (2OE), U5.1 (1OE), U5.24 (4OE), U5.25 (3OE), U5.48 (2OE), U6.1 (1OE), U6.24 (4OE), U6.25 (3OE), U6.48 (2OE), U11.2; also elsewhere on the board
